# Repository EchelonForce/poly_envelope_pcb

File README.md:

# poly_envelope_pcb

This is a PCB design of a Polyphonic Envelope for Eurorack.

Write-up:
https://www.robotdialogs.com/2022/07/eurorack-polyphonic-envelope-generator.html

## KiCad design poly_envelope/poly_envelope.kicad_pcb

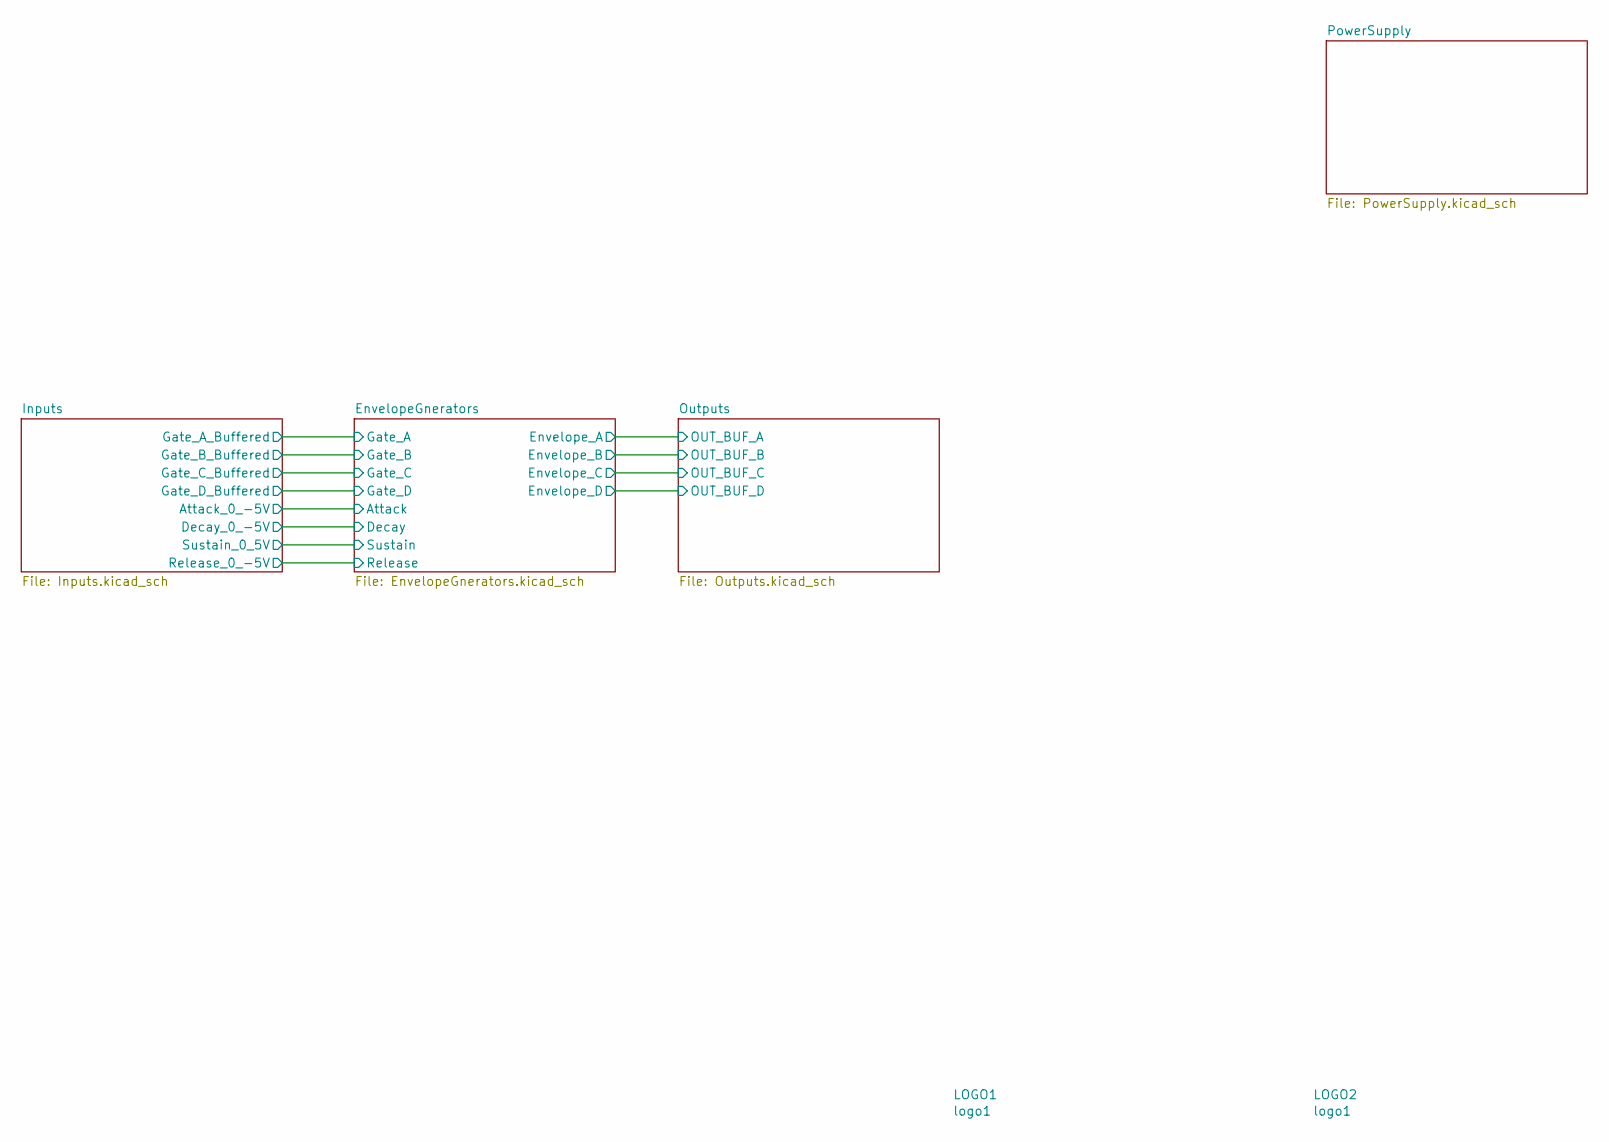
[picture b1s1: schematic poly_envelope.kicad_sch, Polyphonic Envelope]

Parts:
LOGO1, LOGO2: logo1; Logo1

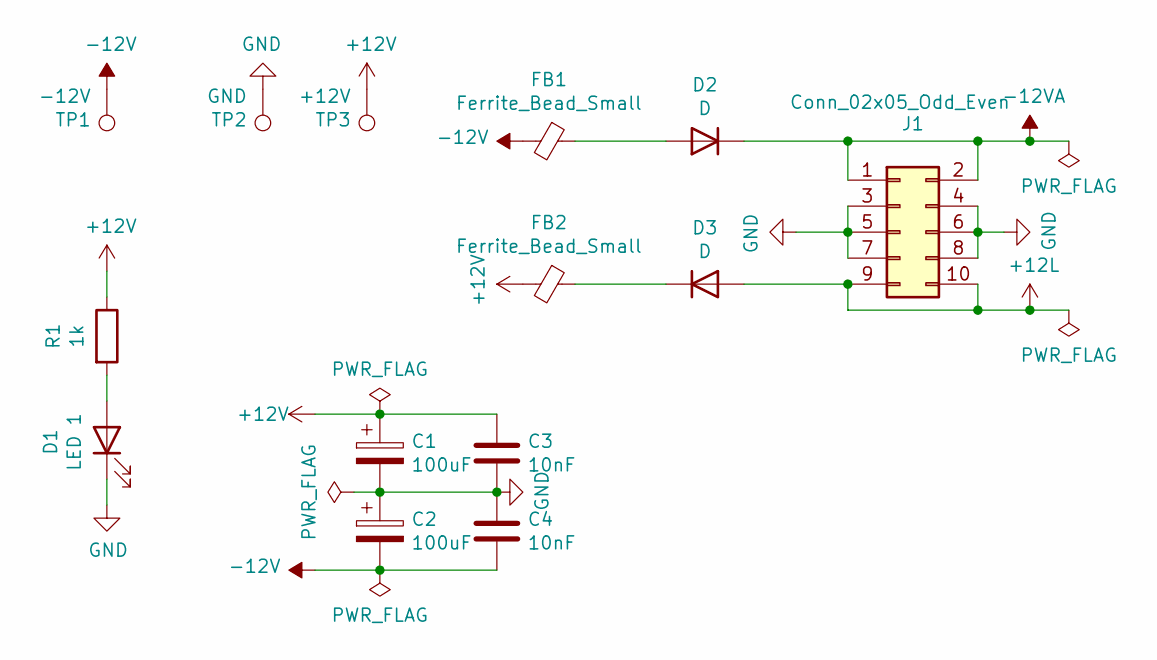
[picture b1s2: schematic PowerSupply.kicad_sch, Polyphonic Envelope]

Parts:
C1, C2: 100uF; CP_Radial_D5.0mm_P2.50mm
C3, C4: 10nF; C_Disc_D5.1mm_W3.2mm_P5.00mm
D1: LED 1; LED_D3.0mm
D2, D3: D; D_A-405_P7.62mm_Horizontal
FB1, FB2: Ferrite_Bead_Small; L_Axial_L5.3mm_D2.2mm_P7.62mm_Horizontal_Vishay_IM-1
J1: Conn_02x05_Odd_Even; IDC-Header_2x05_P2.54mm_Vertical
R1: 1k; R_1206_3216Metric_Pad1.30x1.75mm_HandSolder
TP1: -12V; TestPoint_THTPad_D2.5mm_Drill1.2mm
TP2: GND; TestPoint_THTPad_D2.5mm_Drill1.2mm
TP3: +12V; TestPoint_THTPad_D2.5mm_Drill1.2mm

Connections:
+12L: D3.2 (A), J1.9, J1.10
+12V: C1.1, C3.2, FB2.2, R1.1, TP3.1; also elsewhere on the board
-12V: C2.2, C4.1, FB1.2, TP1.1; also elsewhere on the board
-12VA: D2.1 (K), J1.1, J1.2
GND: C1.2, C2.1, C3.1, C4.2, D1.1 (K), J1.3, J1.4, J1.5, J1.6, J1.7, J1.8, TP2.1; also elsewhere on the board
unnamed: D1.2 (A), R1.2
unnamed: D2.2 (A), FB1.1
unnamed: D3.1 (K), FB2.1

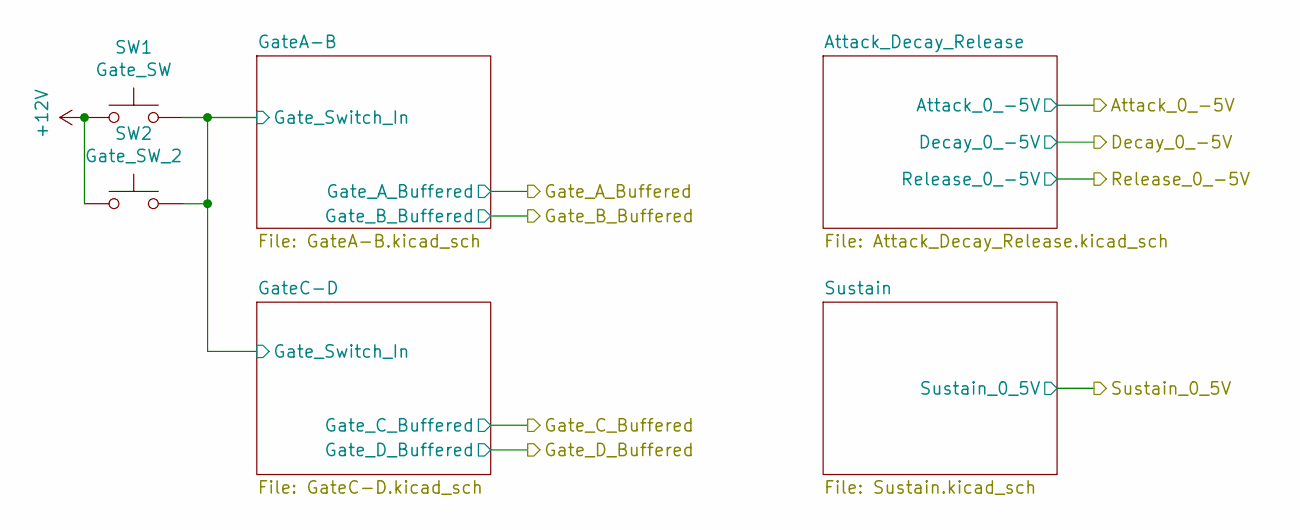
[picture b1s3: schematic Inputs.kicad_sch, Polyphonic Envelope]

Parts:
SW1: Gate_SW; SW_PUSH_6mm_H13mm
SW2: Gate_SW_2; SW_PS1024ALRED

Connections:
+12V: SW1.1, SW2.1; also elsewhere on the board
/Inputs/GateA-B/Gate_Switch_In: SW1.2, SW2.2; also elsewhere on the board

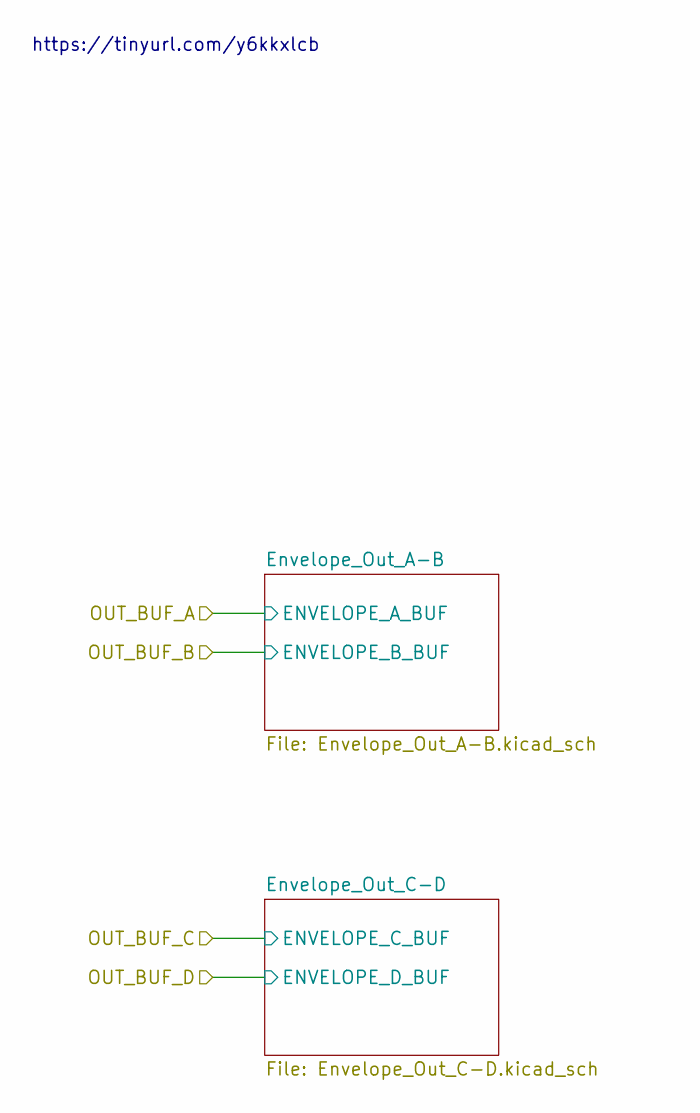
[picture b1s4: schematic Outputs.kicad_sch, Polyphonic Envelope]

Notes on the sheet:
https://tinyurl.com/y6kkxlcb

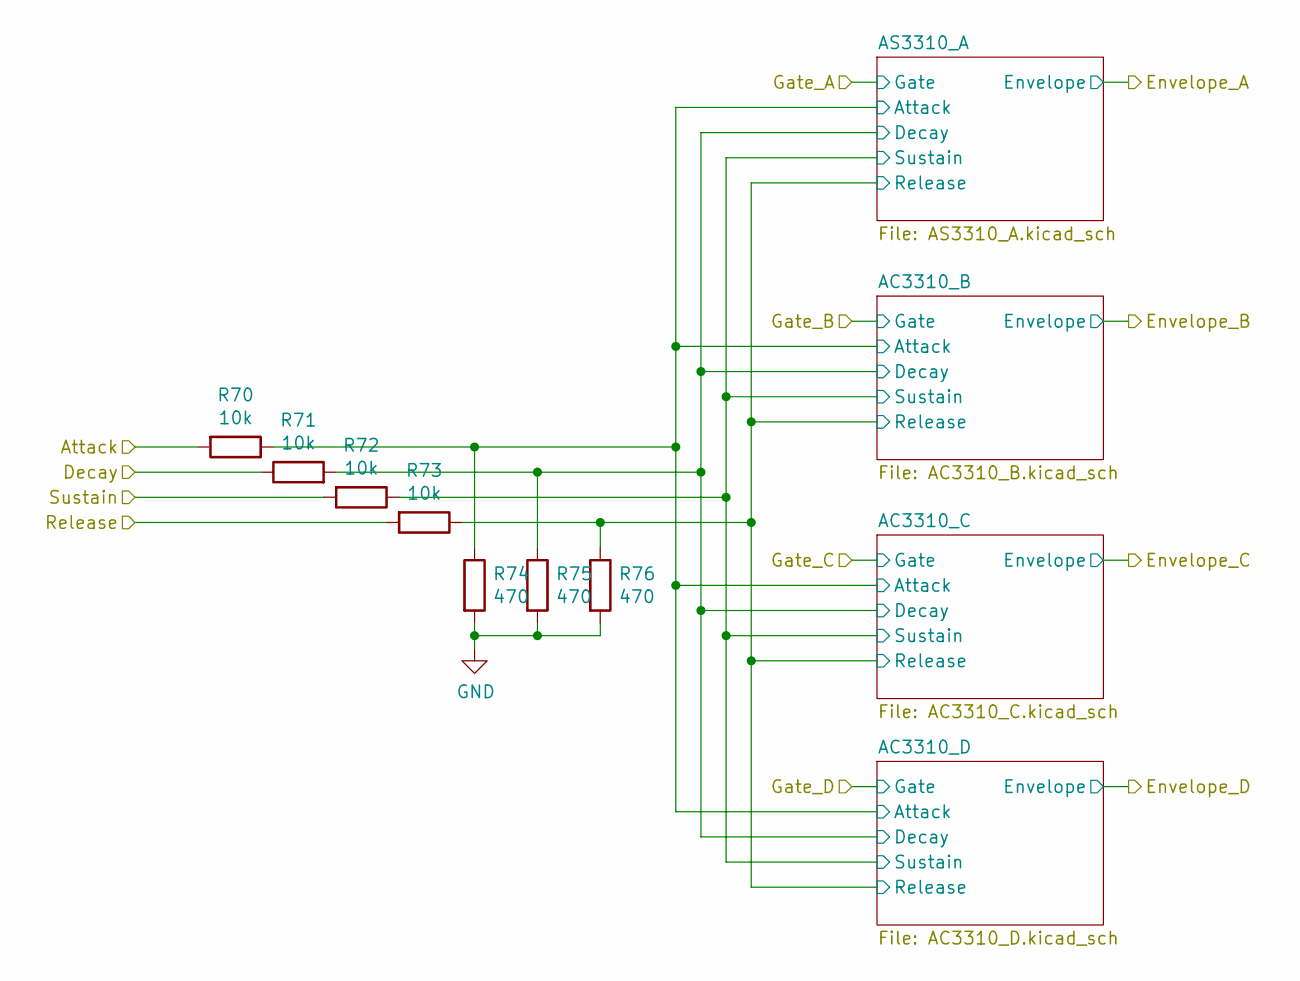
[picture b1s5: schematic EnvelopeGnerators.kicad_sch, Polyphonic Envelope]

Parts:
R70, R71, R72, R73: 10k; R_1206_3216Metric_Pad1.30x1.75mm_HandSolder
R74, R75, R76: 470; R_1206_3216Metric_Pad1.30x1.75mm_HandSolder

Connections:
/EnvelopeGnerators/AC3310_B/Attack: R70.1, R74.1; also elsewhere on the board
/EnvelopeGnerators/AC3310_B/Decay: R71.2, R75.1; also elsewhere on the board
/EnvelopeGnerators/AC3310_B/Release: R73.1, R76.1; also elsewhere on the board
/EnvelopeGnerators/AC3310_B/Sustain: R72.1; also elsewhere on the board
/EnvelopeGnerators/Attack: R70.2; also elsewhere on the board
/EnvelopeGnerators/Decay: R71.1; also elsewhere on the board
/EnvelopeGnerators/Release: R73.2; also elsewhere on the board
/EnvelopeGnerators/Sustain: R72.2; also elsewhere on the board
GND: R74.2, R75.2, R76.2; also elsewhere on the board

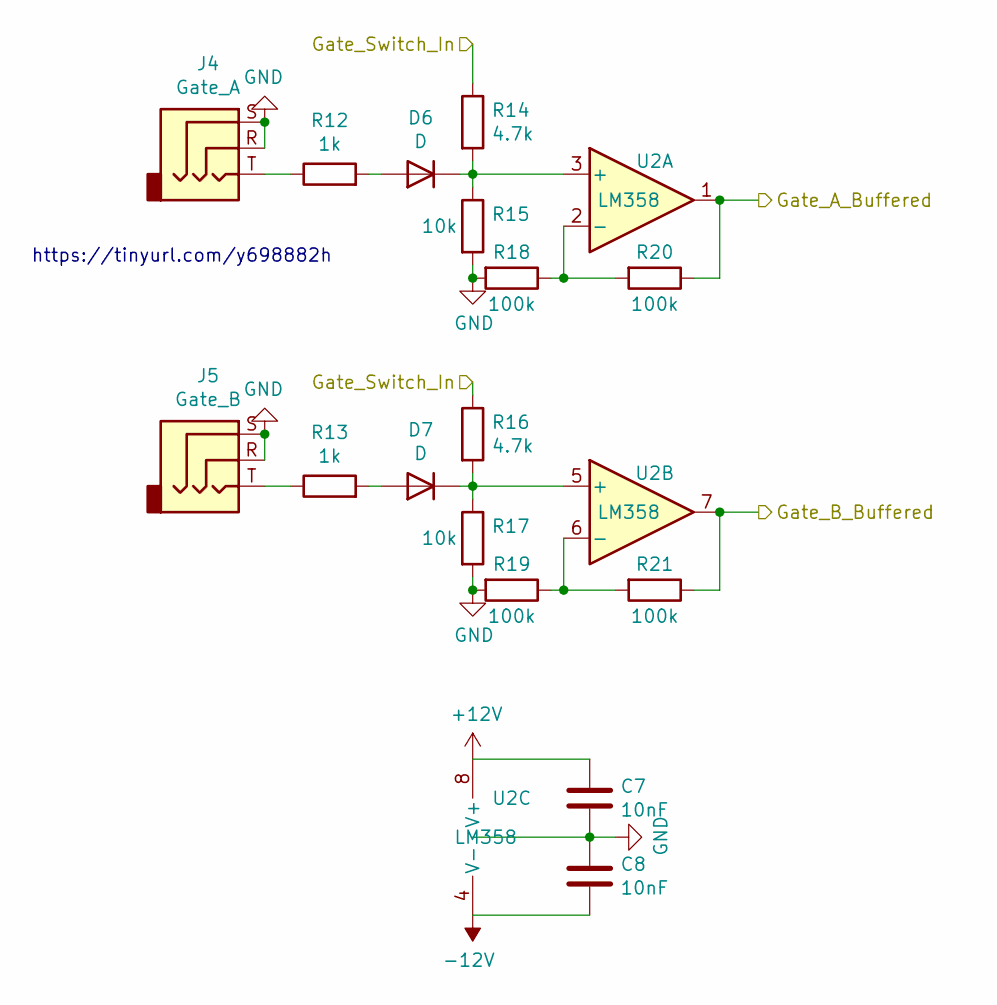
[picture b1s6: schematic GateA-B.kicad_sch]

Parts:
C7, C8: 10nF; C_Disc_D5.1mm_W3.2mm_P5.00mm
D6, D7: D; D_A-405_P7.62mm_Horizontal
J4: Gate_A; Jack_2.5mm_MJ-355W_Vertical
J5: Gate_B; Jack_2.5mm_MJ-355W_Vertical
R12, R13: 1k; R_1206_3216Metric_Pad1.30x1.75mm_HandSolder
R14, R16: 4.7k; R_1206_3216Metric_Pad1.30x1.75mm_HandSolder
R15, R17: 10k; R_1206_3216Metric_Pad1.30x1.75mm_HandSolder
R18, R19, R20, R21: 100k; R_1206_3216Metric_Pad1.30x1.75mm_HandSolder
U2: LM358; DIP-8_W7.62mm

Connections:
+12V: C7.2, U2.8 (V+); also elsewhere on the board
-12V: C8.1, U2.4 (V-); also elsewhere on the board
/EnvelopeGnerators/Gate_A: R20.1, U2.1; also elsewhere on the board
/EnvelopeGnerators/Gate_B: R21.1, U2.7; also elsewhere on the board
/Inputs/GateA-B/Gate_Switch_In: R14.1, R16.1; also elsewhere on the board
GND: C7.1, C8.2, J4.R, J4.S, J5.R, J5.S, R15.2, R17.2, R18.2, R19.2; also elsewhere on the board
unnamed: D6.1 (K), R14.2, R15.1, U2.3 (+)
unnamed: D6.2 (A), R12.2
unnamed: D7.1 (K), R16.2, R17.1, U2.5 (+)
unnamed: D7.2 (A), R13.2
unnamed: J4.T, R12.1
unnamed: J5.T, R13.1
unnamed: R18.1, R20.2, U2.2 (-)
unnamed: R19.1, R21.2, U2.6 (-)

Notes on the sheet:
https://tinyurl.com/y698882h

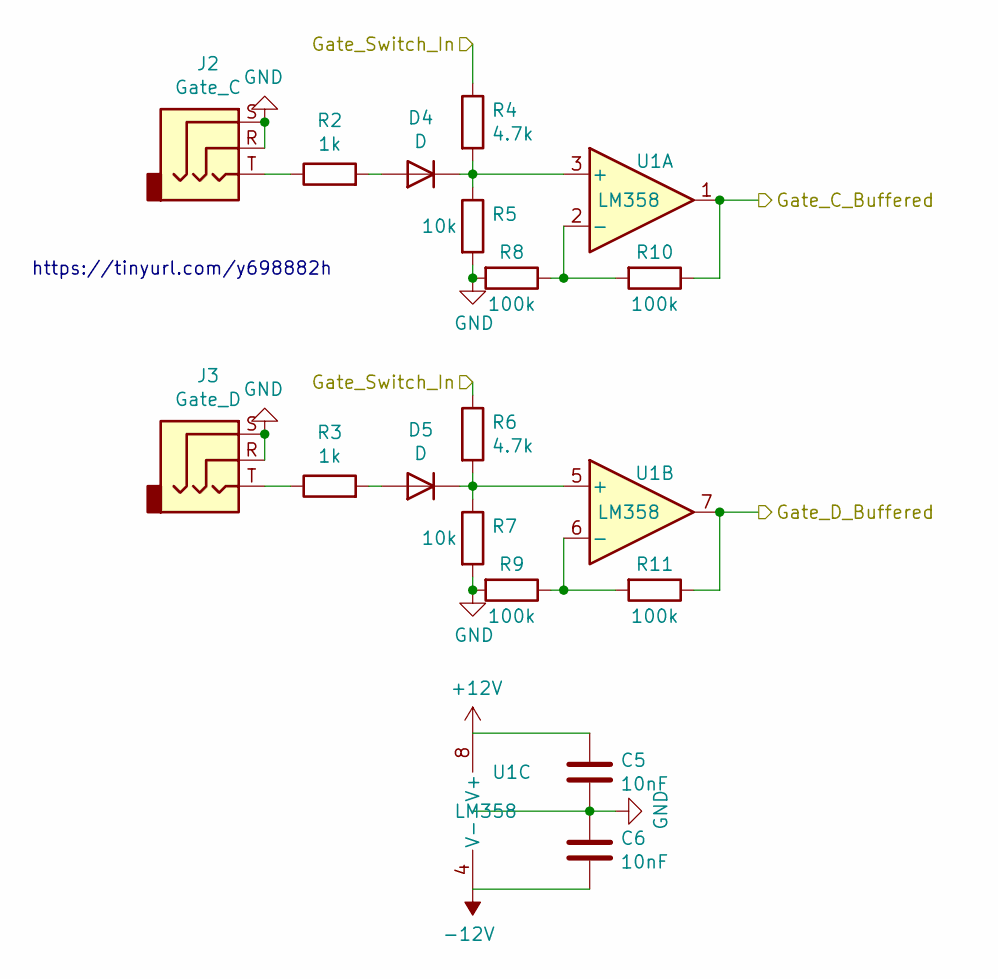
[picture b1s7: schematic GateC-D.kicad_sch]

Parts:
C5, C6: 10nF; C_Disc_D5.1mm_W3.2mm_P5.00mm
D4, D5: D; D_A-405_P7.62mm_Horizontal
J2: Gate_C; Jack_2.5mm_MJ-355W_Vertical
J3: Gate_D; Jack_2.5mm_MJ-355W_Vertical
R2, R3: 1k; R_1206_3216Metric_Pad1.30x1.75mm_HandSolder
R4, R6: 4.7k; R_1206_3216Metric_Pad1.30x1.75mm_HandSolder
R5, R7: 10k; R_1206_3216Metric_Pad1.30x1.75mm_HandSolder
R8, R9, R10, R11: 100k; R_1206_3216Metric_Pad1.30x1.75mm_HandSolder
U1: LM358; DIP-8_W7.62mm

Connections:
+12V: C5.2, U1.8 (V+); also elsewhere on the board
-12V: C6.1, U1.4 (V-); also elsewhere on the board
/EnvelopeGnerators/Gate_C: R10.1, U1.1; also elsewhere on the board
/EnvelopeGnerators/Gate_D: R11.1, U1.7; also elsewhere on the board
/Inputs/GateA-B/Gate_Switch_In: R4.1, R6.1; also elsewhere on the board
GND: C5.1, C6.2, J2.R, J2.S, J3.R, J3.S, R5.2, R7.2, R8.2, R9.2; also elsewhere on the board
unnamed: D4.1 (K), R4.2, R5.1, U1.3 (+)
unnamed: D4.2 (A), R2.2
unnamed: D5.1 (K), R6.2, R7.1, U1.5 (+)
unnamed: D5.2 (A), R3.2
unnamed: J2.T, R2.1
unnamed: J3.T, R3.1
unnamed: R8.1, R10.2, U1.2 (-)
unnamed: R9.1, R11.2, U1.6 (-)

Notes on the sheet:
https://tinyurl.com/y698882h

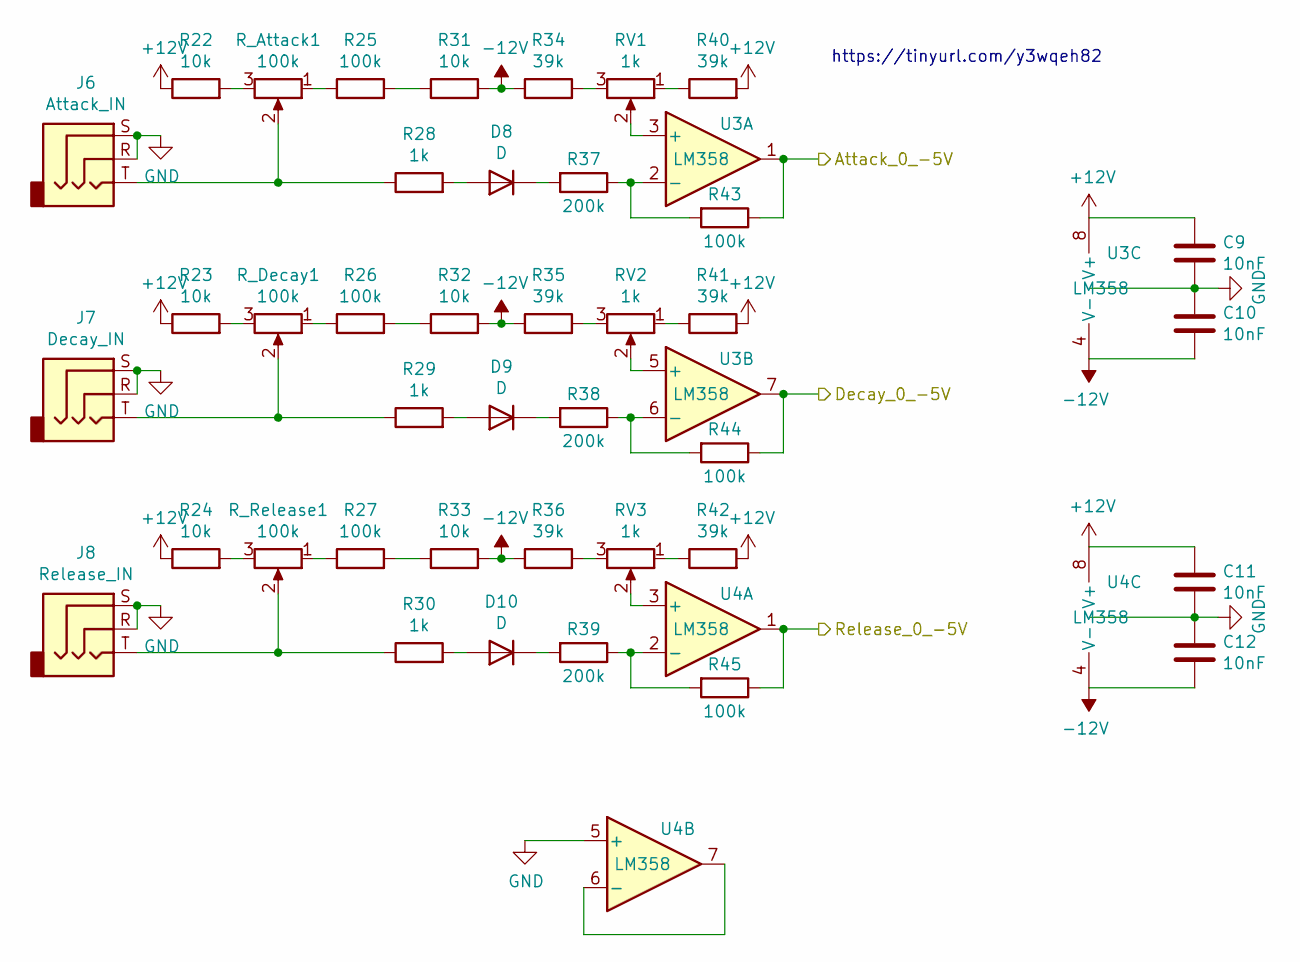
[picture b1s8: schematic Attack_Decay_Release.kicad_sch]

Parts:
C9, C10, C11, C12: 10nF; C_Disc_D5.1mm_W3.2mm_P5.00mm
D8, D9, D10: D; D_A-405_P7.62mm_Horizontal
J6: Attack_IN; Jack_2.5mm_MJ-355W_Vertical
J7: Decay_IN; Jack_2.5mm_MJ-355W_Vertical
J8: Release_IN; Jack_2.5mm_MJ-355W_Vertical
R22, R23, R24, R31, R32, R33: 10k; R_1206_3216Metric_Pad1.30x1.75mm_HandSolder
R25, R26, R27, R43, R44, R45: 100k; R_1206_3216Metric_Pad1.30x1.75mm_HandSolder
R28, R29, R30: 1k; R_1206_3216Metric_Pad1.30x1.75mm_HandSolder
R34, R35, R36, R40, R41, R42: 39k; R_1206_3216Metric_Pad1.30x1.75mm_HandSolder
R37, R38, R39: 200k; R_1206_3216Metric_Pad1.30x1.75mm_HandSolder
RV1, RV2, RV3: 1k; Potentiometer_Bourns_3296W_Vertical
R_Attack1: 100k; Potentiometer_Alpha_RD901F-40-00D_Single_Vertical_w_3d
R_Decay1: 100k; Potentiometer_Alpha_RD901F-40-00D_Single_Vertical_w_3d
R_Release1: 100k; Potentiometer_Alpha_RD901F-40-00D_Single_Vertical_w_3d
U3, U4: LM358; DIP-8_W7.62mm

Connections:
+12V: C9.2, C11.2, R22.1, R23.1, R24.1, R40.2, R41.2, R42.2, U3.8 (V+), U4.8 (V+); also elsewhere on the board
-12V: C10.1, C12.1, R31.2, R32.2, R33.2, R34.1, R35.1, R36.1, U3.4 (V-), U4.4 (V-); also elsewhere on the board
/EnvelopeGnerators/Attack: R43.1, U3.1; also elsewhere on the board
/EnvelopeGnerators/Decay: R44.1, U3.7; also elsewhere on the board
/EnvelopeGnerators/Release: R45.1, U4.1; also elsewhere on the board
GND: C9.1, C10.2, C11.1, C12.2, J6.R, J6.S, J7.R, J7.S, J8.R, J8.S, U4.5 (+); also elsewhere on the board
unnamed: D8.1 (K), R37.2
unnamed: D8.2 (A), R28.2
unnamed: D9.1 (K), R38.2
unnamed: D9.2 (A), R29.2
unnamed: D10.1 (K), R39.2
unnamed: D10.2 (A), R30.2
unnamed: J6.T, R28.1, R_Attack1.2
unnamed: J7.T, R29.1, R_Decay1.2
unnamed: J8.T, R30.1, R_Release1.2
unnamed: R22.2, R_Attack1.3
unnamed: R23.2, R_Decay1.3
unnamed: R24.2, R_Release1.3
unnamed: R25.1, R_Attack1.1
unnamed: R25.2, R31.1
unnamed: R26.1, R_Decay1.1
unnamed: R26.2, R32.1
unnamed: R27.1, R_Release1.1
unnamed: R27.2, R33.1
unnamed: R34.2, RV1.3
unnamed: R35.2, RV2.3
unnamed: R36.2, RV3.3
unnamed: R37.1, R43.2, U3.2 (-)
unnamed: R38.1, R44.2, U3.6 (-)
unnamed: R39.1, R45.2, U4.2 (-)
unnamed: R40.1, RV1.1
unnamed: R41.1, RV2.1
unnamed: R42.1, RV3.1
unnamed: RV1.2, U3.3 (+)
unnamed: RV2.2, U3.5 (+)
unnamed: RV3.2, U4.3 (+)
unnamed: U4.6 (-), U4.7

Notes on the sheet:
https://tinyurl.com/y3wqeh82

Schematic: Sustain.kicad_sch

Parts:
C13, C14: 10nF; C_Disc_D5.1mm_W3.2mm_P5.00mm
D11: D; D_A-405_P7.62mm_Horizontal
J9: Sustain_IN; Jack_2.5mm_MJ-355W_Vertical
R46, R49: 10k; R_1206_3216Metric_Pad1.30x1.75mm_HandSolder
R47, R53, R55, R57: 100k; R_1206_3216Metric_Pad1.30x1.75mm_HandSolder
R48: 1k; R_1206_3216Metric_Pad1.30x1.75mm_HandSolder
R50, R52, R54, R56: 39k; R_1206_3216Metric_Pad1.30x1.75mm_HandSolder
R51: 200k; R_1206_3216Metric_Pad1.30x1.75mm_HandSolder
RV4, RV5: 1k; Potentiometer_Bourns_3296W_Vertical
R_Sustain1: 100k; Potentiometer_Alpha_RD901F-40-00D_Single_Vertical_w_3d
U5: LM358; DIP-8_W7.62mm

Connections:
+12V: C13.2, R46.1, R52.2, R54.1, U5.8 (V+); also elsewhere on the board
-12V: C14.1, R49.2, R50.1, R56.2, U5.4 (V-); also elsewhere on the board
/EnvelopeGnerators/Sustain: R57.1, U5.7; also elsewhere on the board
GND: C13.1, C14.2, J9.R, J9.S; also elsewhere on the board
unnamed: D11.1 (K), R51.2
unnamed: D11.2 (A), R48.2
unnamed: J9.T, R48.1, R_Sustain1.2
unnamed: R46.2, R_Sustain1.3
unnamed: R47.1, R_Sustain1.1
unnamed: R47.2, R49.1
unnamed: R50.2, RV4.3
unnamed: R51.1, R53.2, U5.2 (-)
unnamed: R52.1, RV4.1
unnamed: R53.1, R55.2, U5.1
unnamed: R54.2, RV5.3
unnamed: R55.1, R57.2, U5.6 (-)
unnamed: R56.1, RV5.1
unnamed: RV4.2, U5.3 (+)
unnamed: RV5.2, U5.5 (+)

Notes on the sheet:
https://tinyurl.com/y6jkg6v4

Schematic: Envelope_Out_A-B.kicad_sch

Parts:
C15, C16: 10nF; C_Disc_D5.1mm_W3.2mm_P5.00mm
D16: LED_B; LED_D3.0mm
D17: LED_A; LED_D3.0mm
J10: ENV_B; Jack_2.5mm_MJ-355W_Vertical
J11: ENV_A; Jack_2.5mm_MJ-355W_Vertical
Q1, Q2: 2N3906; TO-92_Inline
R58, R59, R60, R61, R89, R90: 100k; R_1206_3216Metric_Pad1.30x1.75mm_HandSolder
R62, R63: 1k; R_1206_3216Metric_Pad1.30x1.75mm_HandSolder
R91, R92: 22k; R_1206_3216Metric_Pad1.30x1.75mm_HandSolder
R93, R94: 3.3k; R_1206_3216Metric_Pad1.30x1.75mm_HandSolder
RV6, RV7: 100k; Potentiometer_Bourns_3296W_Vertical
U6: TL072; DIP-8_W7.62mm

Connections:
+12V: C15.2, R93.1, R94.1, RV6.1, RV7.1, U6.8 (V+); also elsewhere on the board
-12V: C16.1, RV6.3, RV7.3, U6.4 (V-); also elsewhere on the board
/EnvelopeGnerators/Envelope_A: U6.3 (+); also elsewhere on the board
/EnvelopeGnerators/Envelope_B: U6.5 (+); also elsewhere on the board
GND: C15.1, C16.2, D16.1 (K), D17.1 (K), J10.R, J10.S, J11.R, J11.S, Q1.1 (E), Q2.1 (E), R91.2, R92.2; also elsewhere on the board
unnamed: D16.2 (A), Q1.3 (C), R93.2
unnamed: D17.2 (A), Q2.3 (C), R94.2
unnamed: J10.T, R63.1
unnamed: J11.T, R62.1
unnamed: Q1.2 (B), R89.1, R91.1
unnamed: Q2.2 (B), R90.1, R92.1
unnamed: R58.1, R60.2, U6.2 (-)
unnamed: R58.2, RV6.2
unnamed: R59.1, R61.2, U6.6 (-)
unnamed: R59.2, RV7.2
unnamed: R60.1, R62.2, R90.2, U6.1
unnamed: R61.1, R63.2, R89.2, U6.7

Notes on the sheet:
https://tinyurl.com/2e2j6wnu

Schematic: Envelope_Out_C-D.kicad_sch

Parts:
C17, C18: 10nF; C_Disc_D5.1mm_W3.2mm_P5.00mm
D18: LED_C; LED_D3.0mm
D19: LED_D; LED_D3.0mm
J12: ENV_C; Jack_2.5mm_MJ-355W_Vertical
J13: ENV_D; Jack_2.5mm_MJ-355W_Vertical
Q3, Q4: 2N3906; TO-92_Inline
R64, R65, R66, R67, R95, R96: 100k; R_1206_3216Metric_Pad1.30x1.75mm_HandSolder
R68, R69: 1k; R_1206_3216Metric_Pad1.30x1.75mm_HandSolder
R97, R98: 22k; R_1206_3216Metric_Pad1.30x1.75mm_HandSolder
R99, R100: 3.3k; R_1206_3216Metric_Pad1.30x1.75mm_HandSolder
RV8, RV9: 100k; Potentiometer_Bourns_3296W_Vertical
U7: TL072; DIP-8_W7.62mm

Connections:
+12V: C17.2, R99.1, R100.1, RV8.1, RV9.1, U7.8 (V+); also elsewhere on the board
-12V: C18.1, RV8.3, RV9.3, U7.4 (V-); also elsewhere on the board
/EnvelopeGnerators/Envelope_C: U7.3 (+); also elsewhere on the board
/EnvelopeGnerators/Envelope_D: U7.5 (+); also elsewhere on the board
GND: C17.1, C18.2, D18.1 (K), D19.1 (K), J12.R, J12.S, J13.R, J13.S, Q3.1 (E), Q4.1 (E), R97.2, R98.2; also elsewhere on the board
unnamed: D18.2 (A), Q3.3 (C), R99.2
unnamed: D19.2 (A), Q4.3 (C), R100.2
unnamed: J12.T, R68.1
unnamed: J13.T, R69.1
unnamed: Q3.2 (B), R95.1, R97.1
unnamed: Q4.2 (B), R96.1, R98.1
unnamed: R64.1, R66.2, U7.2 (-)
unnamed: R64.2, RV8.2
unnamed: R65.1, R67.2, U7.6 (-)
unnamed: R65.2, RV9.2
unnamed: R66.1, R68.2, R95.2, U7.1
unnamed: R67.1, R69.2, R96.2, U7.7

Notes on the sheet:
https://tinyurl.com/2e2j6wnu

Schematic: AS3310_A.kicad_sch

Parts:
C19: 3nF; C_Disc_D5.1mm_W3.2mm_P5.00mm
C20, C21, C23: 10nF; C_Disc_D5.1mm_W3.2mm_P5.00mm
C22: 39nF; C_Disc_D5.1mm_W3.2mm_P5.00mm
D12: D; D_A-405_P7.62mm_Horizontal
R77: 10k; R_1206_3216Metric_Pad1.30x1.75mm_HandSolder
R78: 470; R_1206_3216Metric_Pad1.30x1.75mm_HandSolder
R79: 30k; R_1206_3216Metric_Pad1.30x1.75mm_HandSolder
U8: AS3310; DIP-16_W7.62mm

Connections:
+12V: C23.2, U8.11 (VCC); also elsewhere on the board
-12V: C21.2, R78.2; also elsewhere on the board
/EnvelopeGnerators/AC3310_B/Attack: U8.15 (VCA); also elsewhere on the board
/EnvelopeGnerators/AC3310_B/Decay: U8.12 (VCD); also elsewhere on the board
/EnvelopeGnerators/AC3310_B/Release: U8.13 (VCR); also elsewhere on the board
/EnvelopeGnerators/AC3310_B/Sustain: U8.9 (VCS); also elsewhere on the board
/EnvelopeGnerators/Envelope_A: R79.1, U8.2 (ENVOUT); also elsewhere on the board
/EnvelopeGnerators/Gate_A: D12.2 (A); also elsewhere on the board
GND: C20.2, C21.1, C22.2, C23.1, R77.2, U8.7 (PGND), U8.14 (GND); also elsewhere on the board
unnamed: C19.1, D12.1 (K), R77.1, U8.4 (GATE)
unnamed: C19.2, U8.5 (TRIG)
unnamed: C20.1, U8.8 (CCOMP)
unnamed: C22.1, U8.1 (CAP)
unnamed: R78.1, U8.6 (VEE)
unnamed: R79.2, U8.10 (IIN)

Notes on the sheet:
470 = (12-7.5)/0.01

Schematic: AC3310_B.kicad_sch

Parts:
C24: 3nF; C_Disc_D5.1mm_W3.2mm_P5.00mm
C25, C26, C28: 10nF; C_Disc_D5.1mm_W3.2mm_P5.00mm
C27: 39nF; C_Disc_D5.1mm_W3.2mm_P5.00mm
D13: D; D_A-405_P7.62mm_Horizontal
R80: 10k; R_1206_3216Metric_Pad1.30x1.75mm_HandSolder
R81: 470; R_1206_3216Metric_Pad1.30x1.75mm_HandSolder
R82: 30k; R_1206_3216Metric_Pad1.30x1.75mm_HandSolder
U9: AS3310; DIP-16_W7.62mm

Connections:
+12V: C28.2, U9.11 (VCC); also elsewhere on the board
-12V: C26.2, R81.2; also elsewhere on the board
/EnvelopeGnerators/AC3310_B/Attack: U9.15 (VCA); also elsewhere on the board
/EnvelopeGnerators/AC3310_B/Decay: U9.12 (VCD); also elsewhere on the board
/EnvelopeGnerators/AC3310_B/Release: U9.13 (VCR); also elsewhere on the board
/EnvelopeGnerators/AC3310_B/Sustain: U9.9 (VCS); also elsewhere on the board
/EnvelopeGnerators/Envelope_B: R82.1, U9.2 (ENVOUT); also elsewhere on the board
/EnvelopeGnerators/Gate_B: D13.2 (A); also elsewhere on the board
GND: C25.2, C26.1, C27.2, C28.1, R80.2, U9.7 (PGND), U9.14 (GND); also elsewhere on the board
unnamed: C24.1, D13.1 (K), R80.1, U9.4 (GATE)
unnamed: C24.2, U9.5 (TRIG)
unnamed: C25.1, U9.8 (CCOMP)
unnamed: C27.1, U9.1 (CAP)
unnamed: R81.1, U9.6 (VEE)
unnamed: R82.2, U9.10 (IIN)

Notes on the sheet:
470 = (12-7.5)/0.01

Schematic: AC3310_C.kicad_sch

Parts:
C29: 3nF; C_Disc_D5.1mm_W3.2mm_P5.00mm
C30, C31, C33: 10nF; C_Disc_D5.1mm_W3.2mm_P5.00mm
C32: 39nF; C_Disc_D5.1mm_W3.2mm_P5.00mm
D14: D; D_A-405_P7.62mm_Horizontal
R83: 10k; R_1206_3216Metric_Pad1.30x1.75mm_HandSolder
R84: 470; R_1206_3216Metric_Pad1.30x1.75mm_HandSolder
R85: 30k; R_1206_3216Metric_Pad1.30x1.75mm_HandSolder
U10: AS3310; DIP-16_W7.62mm

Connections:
+12V: C33.2, U10.11 (VCC); also elsewhere on the board
-12V: C31.2, R84.2; also elsewhere on the board
/EnvelopeGnerators/AC3310_B/Attack: U10.15 (VCA); also elsewhere on the board
/EnvelopeGnerators/AC3310_B/Decay: U10.12 (VCD); also elsewhere on the board
/EnvelopeGnerators/AC3310_B/Release: U10.13 (VCR); also elsewhere on the board
/EnvelopeGnerators/AC3310_B/Sustain: U10.9 (VCS); also elsewhere on the board
/EnvelopeGnerators/Envelope_C: R85.1, U10.2 (ENVOUT); also elsewhere on the board
/EnvelopeGnerators/Gate_C: D14.2 (A); also elsewhere on the board
GND: C30.2, C31.1, C32.2, C33.1, R83.2, U10.7 (PGND), U10.14 (GND); also elsewhere on the board
unnamed: C29.1, D14.1 (K), R83.1, U10.4 (GATE)
unnamed: C29.2, U10.5 (TRIG)
unnamed: C30.1, U10.8 (CCOMP)
unnamed: C32.1, U10.1 (CAP)
unnamed: R84.1, U10.6 (VEE)
unnamed: R85.2, U10.10 (IIN)

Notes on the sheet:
470 = (12-7.5)/0.01

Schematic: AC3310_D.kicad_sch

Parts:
C34: 3nF; C_Disc_D5.1mm_W3.2mm_P5.00mm
C35, C36, C38: 10nF; C_Disc_D5.1mm_W3.2mm_P5.00mm
C37: 39nF; C_Disc_D5.1mm_W3.2mm_P5.00mm
D15: D; D_A-405_P7.62mm_Horizontal
R86: 10k; R_1206_3216Metric_Pad1.30x1.75mm_HandSolder
R87: 470; R_1206_3216Metric_Pad1.30x1.75mm_HandSolder
R88: 30k; R_1206_3216Metric_Pad1.30x1.75mm_HandSolder
U11: AS3310; DIP-16_W7.62mm

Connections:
+12V: C38.2, U11.11 (VCC); also elsewhere on the board
-12V: C36.2, R87.2; also elsewhere on the board
/EnvelopeGnerators/AC3310_B/Attack: U11.15 (VCA); also elsewhere on the board
/EnvelopeGnerators/AC3310_B/Decay: U11.12 (VCD); also elsewhere on the board
/EnvelopeGnerators/AC3310_B/Release: U11.13 (VCR); also elsewhere on the board
/EnvelopeGnerators/AC3310_B/Sustain: U11.9 (VCS); also elsewhere on the board
/EnvelopeGnerators/Envelope_D: R88.1, U11.2 (ENVOUT); also elsewhere on the board
/EnvelopeGnerators/Gate_D: D15.2 (A); also elsewhere on the board
GND: C35.2, C36.1, C37.2, C38.1, R86.2, U11.7 (PGND), U11.14 (GND); also elsewhere on the board
unnamed: C34.1, D15.1 (K), R86.1, U11.4 (GATE)
unnamed: C34.2, U11.5 (TRIG)
unnamed: C35.1, U11.8 (CCOMP)
unnamed: C37.1, U11.1 (CAP)
unnamed: R87.1, U11.6 (VEE)
unnamed: R88.2, U11.10 (IIN)

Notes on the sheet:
470 = (12-7.5)/0.01

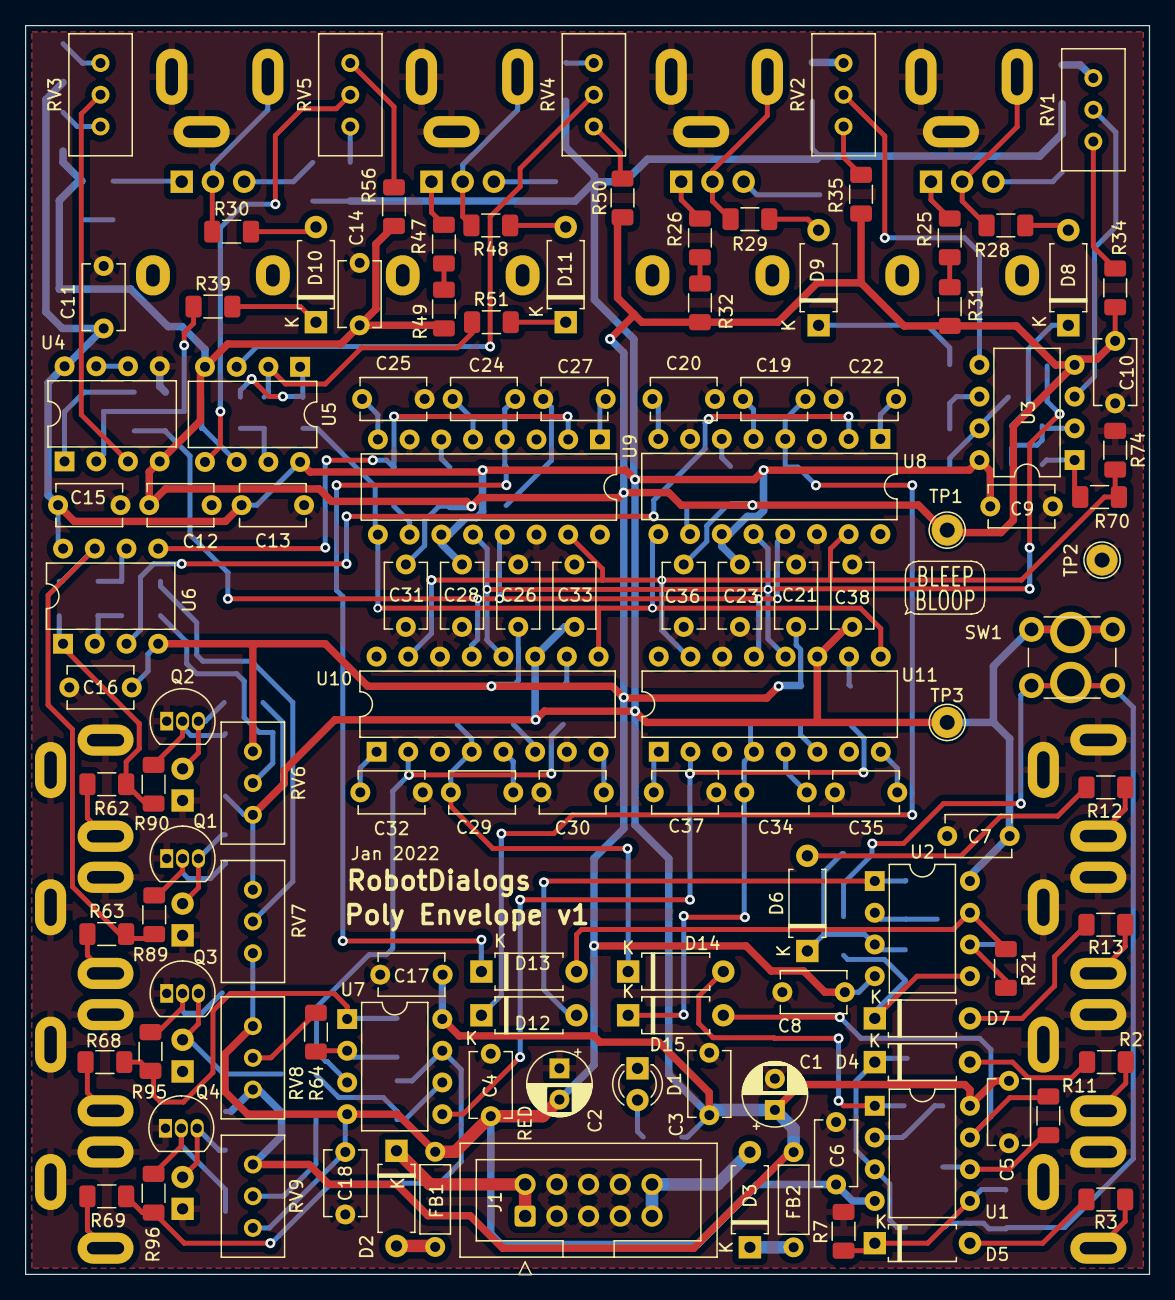
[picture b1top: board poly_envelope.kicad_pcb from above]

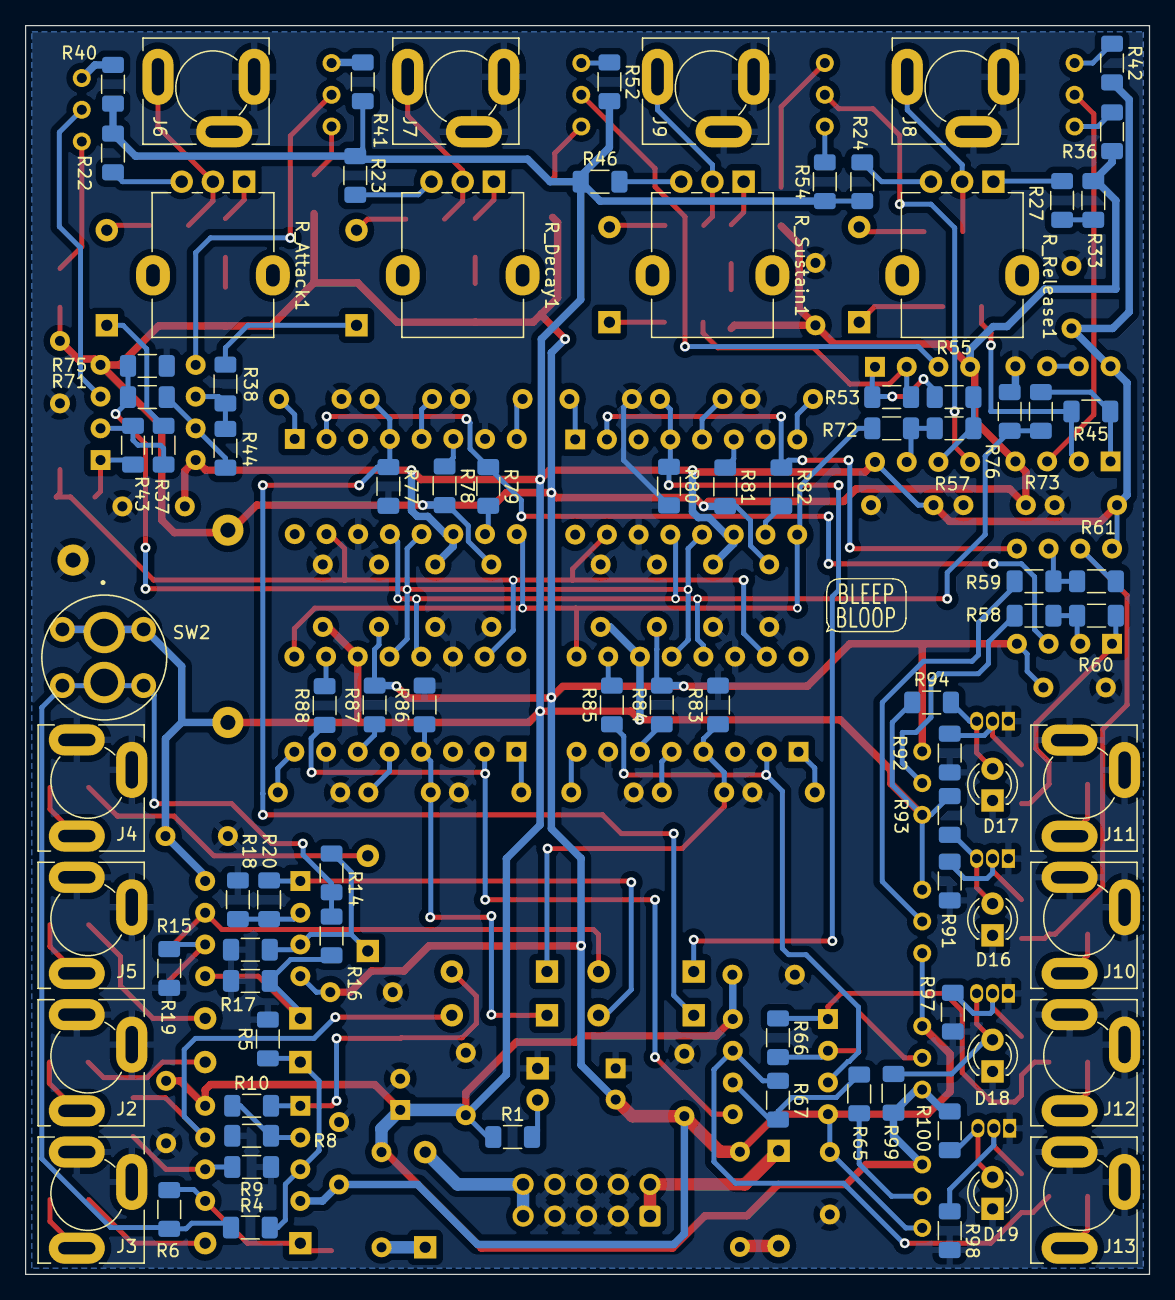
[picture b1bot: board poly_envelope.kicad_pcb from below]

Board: 2 copper layers, 90.0 x 100.0 mm, 207 parts (88 on the bottom side), 135 nets.
